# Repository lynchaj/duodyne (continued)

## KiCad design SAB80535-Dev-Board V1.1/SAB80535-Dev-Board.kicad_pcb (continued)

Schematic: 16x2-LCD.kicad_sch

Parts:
C13: 0.1uF; C_Disc_D5.0mm_W2.5mm_P5.00mm
J9: LCD PWR; PinHeader_2x03_P2.54mm_Vertical
J10: LCD PORT; PinHeader_2x08_P2.54mm_Vertical
RV2: 10K; Potentiometer_Bourns_3386P_Vertical

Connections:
A0: J10.5; also elsewhere on the board
A1: J10.4; also elsewhere on the board
D0: J10.7; also elsewhere on the board
D1: J10.8; also elsewhere on the board
D2: J10.9; also elsewhere on the board
D3: J10.10; also elsewhere on the board
D4: J10.11; also elsewhere on the board
D5: J10.12; also elsewhere on the board
D6: J10.13; also elsewhere on the board
D7: J10.14; also elsewhere on the board
E: J10.6; also elsewhere on the board
GND: C13.2, J9.1, J9.2, J10.16, RV2.3; also elsewhere on the board
LCD-ADJ: C13.1, J10.3, RV2.2
LCD-PWR1: J9.4, J10.1
LCD-PWR2: J9.3, J10.2
VCC: J9.5, J9.6, J10.15, RV2.1; also elsewhere on the board

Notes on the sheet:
NOTE: LCD APPEARS AT ~{CS-LCD} FF08-FF0B
NOTE: HD44780 interface https://www.pololu.com/product/773 16x2 2-LINE LCD DISPLAY

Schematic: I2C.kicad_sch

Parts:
BT1: Battery; BatteryHolder_Keystone_103_1x20mm
Brd1: SSD1306; 128x64OLED
J22: EXT I2C; PinHeader_1x04_P2.54mm_Vertical
J23: I2C INT; PinHeader_1x03_P2.54mm_Vertical
R15: 4700; R_Axial_DIN0207_L6.3mm_D2.5mm_P7.62mm_Horizontal
R18, R19: 10K; R_Axial_DIN0207_L6.3mm_D2.5mm_P7.62mm_Horizontal
U19: PCF8584; DIP-20_W7.62mm_Socket
U24: DS1307+; DIP-8_W7.62mm_Socket
X1: 32.768 KHz; Crystal_AT310_D3.0mm_L10.0mm_Horizontal

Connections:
/I2C/VBAT: BT1.1 (+), U24.3 (VBAT)
A0: U19.6 (A0); also elsewhere on the board
CLK: U19.1 (CLK); also elsewhere on the board
D0: U19.7 (D0); also elsewhere on the board
D1: U19.8 (D1); also elsewhere on the board
D2: U19.9 (D2); also elsewhere on the board
D3: U19.11 (D3); also elsewhere on the board
D4: U19.12 (D4); also elsewhere on the board
D5: U19.13 (D5); also elsewhere on the board
D6: U19.14 (D6); also elsewhere on the board
D7: U19.15 (D7); also elsewhere on the board
GND: BT1.2 (-), Brd1.1 (GND), J22.1, U19.10 (VSS), U24.4 (GND); also elsewhere on the board
I2C-SCL: Brd1.3 (SCL), J22.3, R18.1, U19.3 (SCL), U24.6 (SCL); also elsewhere on the board
I2C-SDA: Brd1.4 (SDA), J22.4, R19.1, U19.2 (SDA), U24.5 (SDA); also elsewhere on the board
unnamed: J23.2, R15.1, U19.5 (~INT)
unnamed: U24.1 (X1), X1.2
unnamed: U24.2 (X2), X1.1
VCC: Brd1.2 (VCC), J22.2, R15.2, R18.2, R19.2, U19.20 (VDD), U24.8 (VCC); also elsewhere on the board
~CS-I2C-WR: U19.18 (~WR); also elsewhere on the board
~CS-I2C: U19.17 (~CS); also elsewhere on the board
~INT0: J23.1; also elsewhere on the board
~INT1: J23.3; also elsewhere on the board
~OE: U19.16 (~RD); also elsewhere on the board
~RES-OUT: U19.19 (~RST); also elsewhere on the board

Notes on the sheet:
SSD1306 OLED 128x64 DISPLAY

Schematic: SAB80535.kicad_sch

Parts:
C31: 10u; CP_Radial_D5.0mm_P2.50mm
C33: 0.1uF; C_Disc_D5.0mm_W2.5mm_P5.00mm
D34: 1N4148; D_DO-35_SOD27_P7.62mm_Horizontal
J13: ~{PE} ~{EA}; PinHeader_2x03_P2.54mm_Vertical
J14: CMOS; PinHeader_1x02_P2.54mm_Vertical
J15: P1; IDC-Header_2x05_P2.54mm_Horizontal
J16: FE SS; PinHeader_1x04_P2.54mm_Vertical
J18: SAB80535; IDC-Header_2x13_P2.54mm_Horizontal
J19: MAIN & AUX SERIAL; IDC-Header_2x06_P2.54mm_Horizontal
J20: EXP BUS; IDC-Header_2x25_P2.54mm_Horizontal
J21: NMOS; PinHeader_1x02_P2.54mm_Vertical
J24: EXT RES; PinHeader_1x02_P2.54mm_Vertical
JP3: SER PWR MAIN; PinHeader_1x02_P2.54mm_Vertical
JP4: SER PWR AUX; PinHeader_1x02_P2.54mm_Vertical
JP5: RES SEL; PinHeader_1x03_P2.54mm_Vertical
R16: 10; R_Axial_DIN0207_L6.3mm_D2.5mm_P7.62mm_Horizontal
R17: 10K; R_Axial_DIN0207_L6.3mm_D2.5mm_P7.62mm_Horizontal
RN10: 10K; R_Array_SIP9
SW2: RESET; SW_PUSH_6mm
U12: SAB80C535; PLCC-68_THT-Socket
U13: 74LS373; DIP-20_W7.62mm_Socket
U16: 74LS74; DIP-14_W7.62mm_Socket
U20: 11.0592 MHz; DIP-14_W7.62mm_Socket
U21: DS1233; TO-92L_HandSolder

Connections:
/SAB80535/VBB: C33.1, J14.2, U12.37 (VCC)
A0: J20.5, U13.2 (O0); also elsewhere on the board
A1: J20.4, U13.5 (O1); also elsewhere on the board
A2: J20.3, U13.6 (O2); also elsewhere on the board
A3: J20.6, U13.9 (O3); also elsewhere on the board
A4: J20.9, U13.12 (O4); also elsewhere on the board
A5: J20.2, U13.15 (O5); also elsewhere on the board
A6: J20.7, U13.16 (O6); also elsewhere on the board
A7: J20.8, U13.19 (O7); also elsewhere on the board
A8: J20.10, U12.41 (P2.0); also elsewhere on the board
A9: J20.14, U12.42 (P2.1); also elsewhere on the board
A10: J20.12, U12.43 (P2.2); also elsewhere on the board
A11: J20.23, U12.44 (P2.3); also elsewhere on the board
A12: U12.45 (P2.4); also elsewhere on the board
A13: U12.46 (P2.5); also elsewhere on the board
A14: U12.47 (P2.6); also elsewhere on the board
A15: U12.48 (P2.7); also elsewhere on the board
ALE: U12.50 (ALE), U13.11 (LE); also elsewhere on the board
CLK: J20.11, U12.39 (XTAL2), U16.9 (Q); also elsewhere on the board
D0: J20.48, RN10.2 (R1), U12.52 (P0.0), U13.3 (D0), U16.2 (D); also elsewhere on the board
D1: J20.46, RN10.3 (R2), U12.53 (P0.1), U13.4 (D1); also elsewhere on the board
D2: J20.47, RN10.4 (R3), U12.54 (P0.2), U13.7 (D2); also elsewhere on the board
D3: J20.45, RN10.5 (R4), U12.55 (P0.3), U13.8 (D3); also elsewhere on the board
D4: J20.42, RN10.6 (R5), U12.56 (P0.4), U13.13 (D4); also elsewhere on the board
D5: J20.43, RN10.7 (R6), U12.57 (P0.5), U13.14 (D5); also elsewhere on the board
D6: J20.41, RN10.8 (R7), U12.58 (P0.6), U13.17 (D6); also elsewhere on the board
D7: J20.44, RN10.9 (R8), U12.59 (P0.7), U13.18 (D7); also elsewhere on the board
GND: C31.2, C33.2, J13.1, J13.2, J15.10, J16.2, J16.3, J18.26, J19.1, J19.2, J20.49, J20.50, J21.1, J24.2, SW2.2, U12.12 (VAGND), U12.38 (GND), U13.1 (OE), U13.10 (GND), U16.11 (C), U16.12 (D), U16.13 (~R), U20.4, U20.7, U21.1; also elsewhere on the board
I2C-SCL: J20.37; also elsewhere on the board
I2C-SDA: J20.39; also elsewhere on the board
unnamed: J19.5, JP3.2 (B)
unnamed: J19.6, JP4.2 (B)
unnamed: J21.2, U12.40 (XTAL1)
unnamed: J24.1, JP5.3, R16.1, SW2.1
unnamed: U16.10 (~S), U20.8, U20.11
ONE: U16.4 (~S); also elsewhere on the board
P1.0: J15.2, U12.36 (P1.0/~INT3/CC0); also elsewhere on the board
P1.1: J15.4, U12.35 (P1.1/INT4/CC1); also elsewhere on the board
P1.2: J15.6, U12.34 (P1.2/INT5/CC2); also elsewhere on the board
P1.3: J15.8, U12.33 (P1.3/INT6/CC3); also elsewhere on the board
P1.4: J15.7, U12.32 (P1.4/~INT2); also elsewhere on the board
P1.5: J15.5, U12.31 (P1.5/T2EX); also elsewhere on the board
P1.6: J15.3, U12.30 (P1.6/CLKOUT); also elsewhere on the board
P1.7: J15.1, U12.29 (P1.7/T2); also elsewhere on the board
P4.0: J18.2, U12.1 (P4.0); also elsewhere on the board
P4.1: J18.4, U12.2 (P4.1); also elsewhere on the board
P4.2: J18.6, U12.3 (P4.2); also elsewhere on the board
P4.3: J18.8, U12.5 (P4.3); also elsewhere on the board
P4.4: J18.10, U12.6 (P4.4); also elsewhere on the board
P4.5: J18.12, U12.7 (P4.5); also elsewhere on the board
P4.6: J18.14, U12.8 (P4.6); also elsewhere on the board
P4.7: J18.16, U12.9 (P4.7); also elsewhere on the board
P5.0: J18.18, U12.67 (P5.0); also elsewhere on the board
P5.1: J18.20, U12.66 (P5.1); also elsewhere on the board
P5.2: J18.22, U12.65 (P5.2); also elsewhere on the board
P5.3: J18.24, U12.64 (P5.3); also elsewhere on the board
P5.4: J18.23, U12.63 (P5.4); also elsewhere on the board
P5.5: J18.21, U12.62 (P5.5); also elsewhere on the board
P5.6: J18.19, U12.61 (P5.6); also elsewhere on the board
P5.7: J18.17, U12.60 (P5.7); also elsewhere on the board
P6.0: J18.1, U12.20 (P6.0)
P6.1: J18.3, U12.19 (P6.1)
P6.2: J18.5, U12.18 (P6.2)
P6.3: J18.7, U12.17 (P6.3)
P6.4: J18.9, U12.16 (P6.4)
P6.5: J18.11, U12.15 (P6.5)
P6.6: J18.13, U12.14 (P6.6)
P6.7: J18.15, U12.13 (P6.7)
RxD: U12.21 (P3.0/RxD); also elsewhere on the board
RxD-0: J19.7; also elsewhere on the board
RxD-1: J19.8; also elsewhere on the board
T0: U12.25 (P3.4/T0); also elsewhere on the board
T1: J16.4, U12.26 (P3.5/T1); also elsewhere on the board
TxD: U12.22 (P3.1/TxD); also elsewhere on the board
TxD-0: J19.9; also elsewhere on the board
TxD-1: J19.10; also elsewhere on the board
VCC: D34.1 (K), J13.5, J13.6, J14.1, J15.9, J18.25, J20.1, J20.22, JP3.1 (A), JP4.1 (A), R17.2, RN10.1 (common), U12.11 (VAREF), U12.68 (VCC), U13.20 (VCC), U20.1, U20.14, U21.3; also elsewhere on the board
ZA14: J20.24; also elsewhere on the board
ZA15: J20.25; also elsewhere on the board
ZA16: J20.28; also elsewhere on the board
ZA17: J20.27; also elsewhere on the board
ZA18: J20.30; also elsewhere on the board
ZA19: J20.29; also elsewhere on the board
ZA20: J20.32; also elsewhere on the board
ZA21: J20.31; also elsewhere on the board
~CS-FF-WR: U16.3 (C); also elsewhere on the board
~EA: J13.4, U12.51 (~EA)
~INT0: J20.33, U12.23 (P3.2/~INT0); also elsewhere on the board
~INT1: J16.1, J20.35, U12.24 (P3.3/~INT1); also elsewhere on the board
~OE: J20.26; also elsewhere on the board
~PAGE-EN: U16.6 (~Q); also elsewhere on the board
~PE: J13.3, U12.4 (~PE)
~PSEN: U12.49 (~PSEN); also elsewhere on the board
~RD: U12.28 (P3.7/~RD); also elsewhere on the board
~RES-IN: J20.40, JP5.2
~RES-OUT: C31.1, D34.2 (A), J20.38, JP5.1, R16.2, R17.1, U12.10 (~RESET), U16.1 (~R), U21.2; also elsewhere on the board
~WR: J20.21, U12.27 (P3.6/~WR); also elsewhere on the board
~Y1: J20.19; also elsewhere on the board
~Y2: J20.18; also elsewhere on the board
~Y7: J20.13; also elsewhere on the board

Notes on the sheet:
NOTE: SAB80C535 RESET IS ACTIVE LOW
NOTE: EXTERNAL PERIPHERALS APPEAR AT MEMORY LOCATIONS Y1 0xFF20-0xFF3F Y2 0xFF40-0xFF5F Y3 0xFF60-0xFF7F Y4 0xFF80-0xFF9F Y5 0xFFA0-0xFFBF Y6 0xFFC0-0xFFDF Y7 0xFFE0-0xFFFF
D-FLIP FLOP AS AN INVERTING DRIVER
JP14 NOTE: RESET SELECT ALLOWS FOR RESET TO ORIGINATE: 1. ON PROCESSOR BOARD RESET BUTTON CIRCUIT ONLY (NONE) 2. FROM EXTERNAL BUS ~{RES-IN} (1-2 CLOSED) 3. TRANSMITTED TO EXTERNAL BUS (2-3 CLOSED)
SINGLE STEP
~{EA} MUST BE TIED TO GND FOR SAB80535 OR SAB80C535 ACCESS EXTERNAL MEMORY
FLASH ERASE
~{PE} MUST BE TIED TO GND FOR SAB80C535 POWER SAVING MODES
P0.0-P0.7 MUST HAVE EXTERNAL PULL UP RESISTORS DURING PROGRAM VERIFICATION (SAB80C515 ONLY)

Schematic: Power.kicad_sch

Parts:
C14, C15, C16, C17, C18, C19, C20, C22, C23, C25, C27, C28, C32, C34, C36, C37, C38, C41, C42, C43: 0.1uF; C_Disc_D5.0mm_W2.5mm_P5.00mm
C21, C24, C26: 10uF; CP_Radial_D5.0mm_P2.50mm
C29, C30: 10u; CP_Radial_D5.0mm_P2.50mm
D10: 1N5819; D_DO-41_SOD81_P10.16mm_Horizontal
D11: VDD; LED_D3.0mm
D40: 9VDC; LED_D3.0mm
H1, H2, H3, H4: MountingHole; MountingHole_3.2mm_M3_Pad
J11: Barrel_Jack_MountingPin; BarrelJack_Horizontal
J12: 9VDC; TerminalBlock_Phoenix_MKDS-1,5-2-5.08_1x02_P5.08mm_Horizont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
NT1, NT3: NetTie_2; NetTie-2_THT_Pad0.3mm
R8: 470; R_Axial_DIN0207_L6.3mm_D2.5mm_P7.62mm_Horizontal
R12: 10K; R_Axial_DIN0207_L6.3mm_D2.5mm_P7.62mm_Horizontal
TP1: VCC; PinHeader_1x01_P2.54mm_Vertical
TP2: GND; PinHeader_1x01_P2.54mm_Vertical
U5: LM7805_TO220; TO-220-3_Horizontal_TabDown
U6: LP2950-3.3_TO92; TO-92_HandSolder

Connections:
/Power/9VDC: C18.1, D10.2 (A), J11.1, J12.1, R12.2
/Power/VI: C21.1, D10.1 (K), U5.1 (VI)
GND: C14.2, C15.2, C16.2, C17.2, C18.2, C19.2, C20.2, C21.2, C22.2, C23.2, C24.2, C25.2, C26.2, C27.2, C28.2, C29.2, C30.2, C32.2, C34.2, C36.2, C37.2, C38.2, C41.2, C42.2, C43.2, D11.1 (K), D40.1 (K), H1.1, H2.1, H3.1, H4.1, J11.2, J11.MP (MountPin), J12.2, NT1.1, TP2.1, U5.2 (GND), U6.2 (GND); also elsewhere on the board
unnamed: D11.2 (A), R8.1
unnamed: D40.2 (A), R12.1
ONE: NT3.2; also elsewhere on the board
VCC: C14.1, C15.1, C16.1, C17.1, C19.1, C20.1, C22.1, C23.1, C24.1, C25.1, C26.1, C27.1, C28.1, C29.1, C32.1, C34.1, C36.1, C37.1, C38.1, C41.1, C42.1, C43.1, NT3.1, TP1.1, U5.3 (VO), U6.3 (VI); also elsewhere on the board
VDD1: C30.1, R8.2, U6.1 (VO); also elsewhere on the board
ZERO: NT1.2; also elsewhere on the board

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
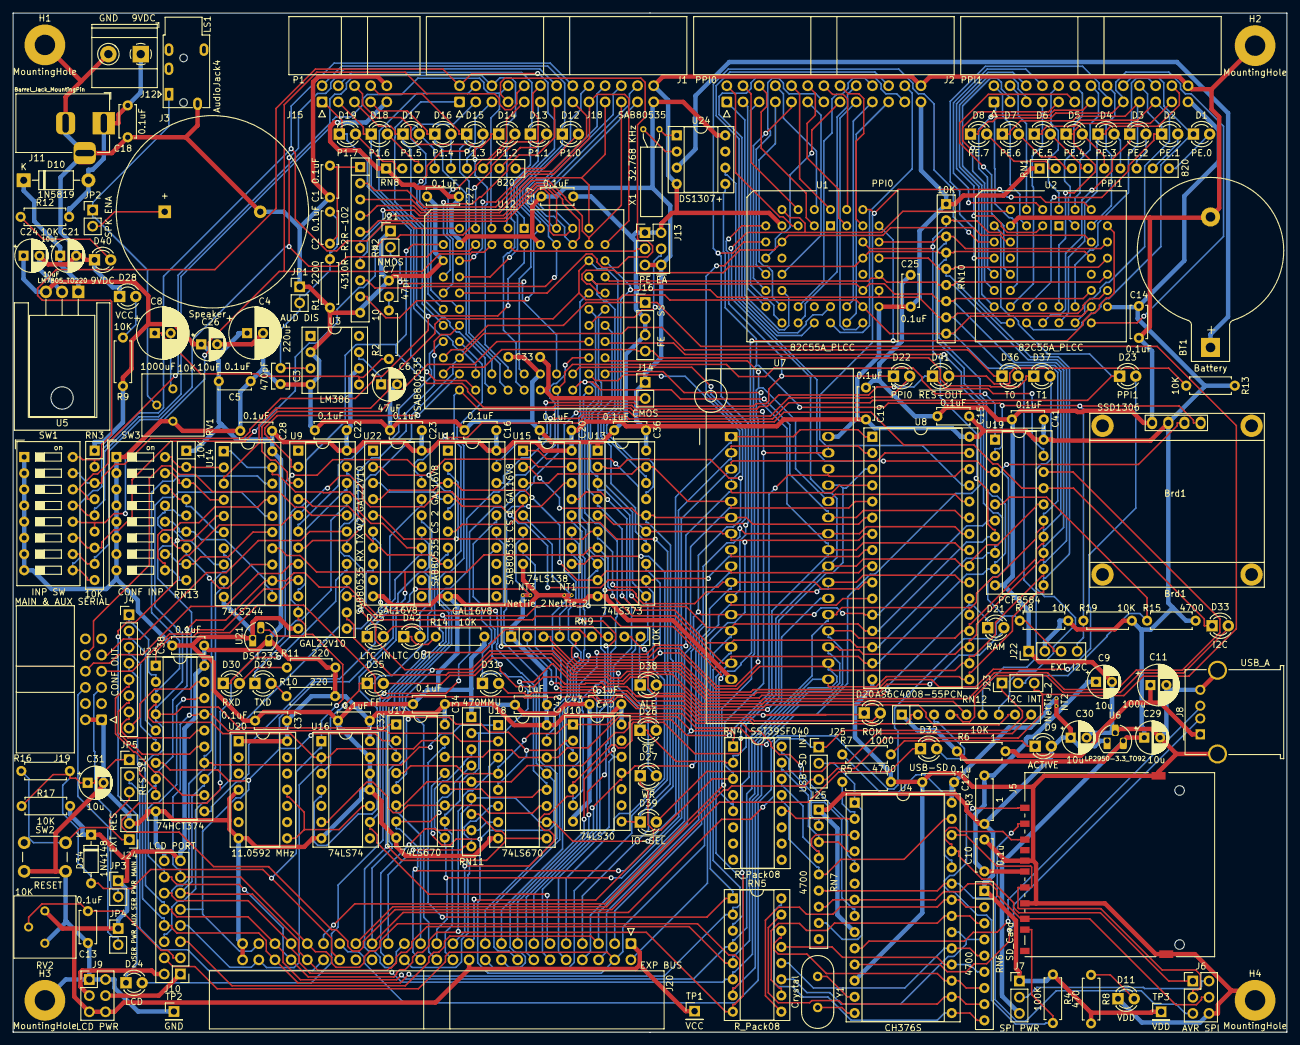
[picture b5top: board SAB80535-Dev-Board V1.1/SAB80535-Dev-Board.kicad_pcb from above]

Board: 2 copper layers, 200.0 x 160.0 mm, 187 parts (1 on the bottom side), 274 nets.

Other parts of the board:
RN11: 470; R_Array_SIP9
U17, U18: 74LS670; DIP-16_W7.62mm_Socket

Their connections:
A0: U17.14 (Wa), U18.14 (Wa); also elsewhere on the board
A1: U17.13 (Wb), U18.13 (Wb); also elsewhere on the board
A14: U17.5 (Ra), U18.5 (Ra); also elsewhere on the board
A15: U17.4 (Rb), U18.4 (Rb); also elsewhere on the board
D0: U17.15 (D1); also elsewhere on the board
D1: U17.1 (D2); also elsewhere on the board
D2: U17.2 (D3); also elsewhere on the board
D3: U17.3 (D4); also elsewhere on the board
D4: U18.15 (D1); also elsewhere on the board
D5: U18.1 (D2); also elsewhere on the board
D6: U18.2 (D3); also elsewhere on the board
D7: U18.3 (D4); also elsewhere on the board
GND: RN11.1 (common), U17.8 (GND), U18.8 (GND); also elsewhere on the board
VCC: U17.16 (VCC), U18.16 (VCC); also elsewhere on the board
ZA14: RN11.2 (R1), U17.10 (Q1); also elsewhere on the board
ZA15: RN11.3 (R2), U17.9 (Q2); also elsewhere on the board
ZA16: RN11.4 (R3), U17.7 (Q3); also elsewhere on the board
ZA17: RN11.5 (R4), U17.6 (Q4); also elsewhere on the board
ZA18: RN11.6 (R5), U18.10 (Q1); also elsewhere on the board
ZA19: RN11.7 (R6), U18.9 (Q2); also elsewhere on the board
ZA20: RN11.8 (R7), U18.7 (Q3); also elsewhere on the board
ZA21: RN11.9 (R8), U18.6 (Q4); also elsewhere on the board
~CS-MMU-WR: U17.12 (~Ew), U18.12 (~Ew); also elsewhere on the board
~PAGE-EN: U17.11 (~Er), U18.11 (~Er); also elsewhere on the board

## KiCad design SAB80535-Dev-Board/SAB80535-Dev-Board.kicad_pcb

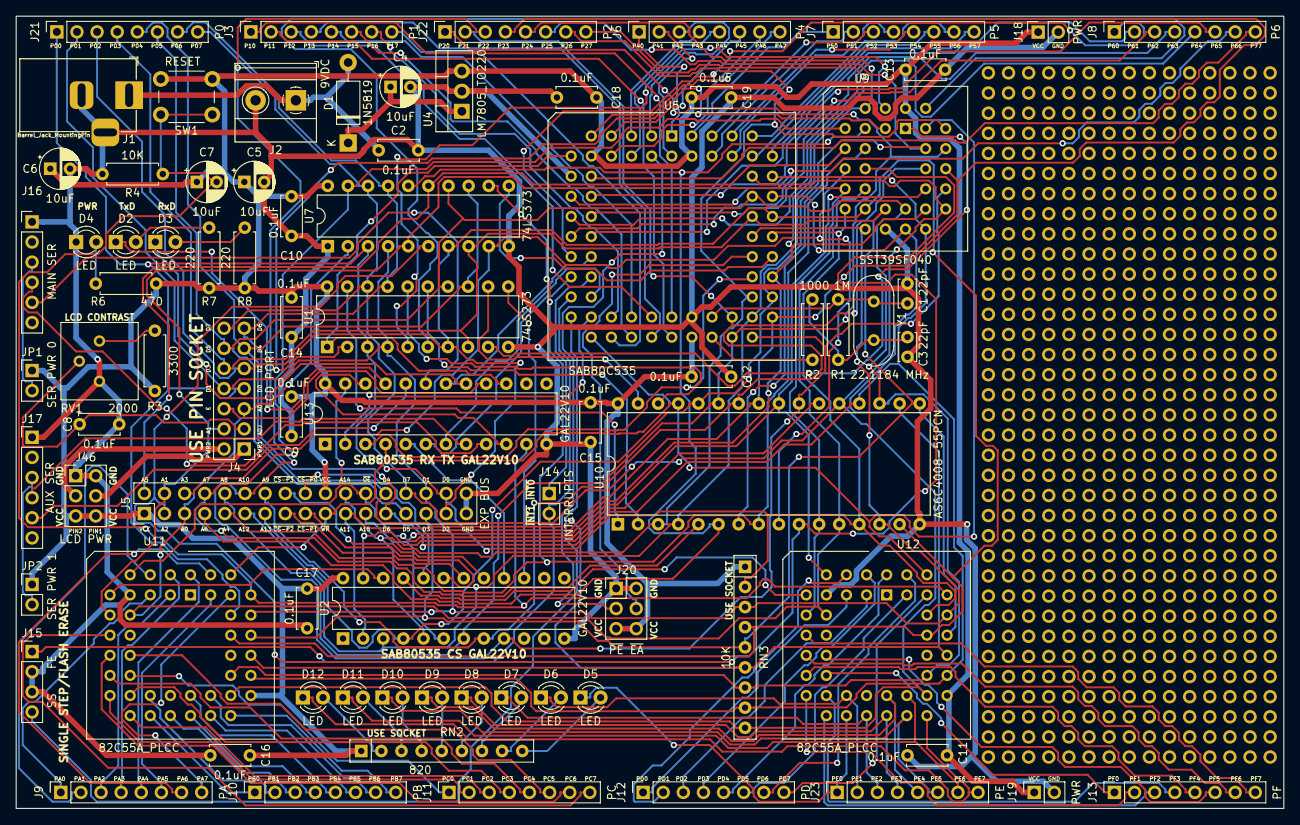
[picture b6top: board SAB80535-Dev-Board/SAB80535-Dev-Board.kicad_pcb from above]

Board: 2 copper layers, 160.0 x 100.0 mm, 100 parts (0 on the bottom side), 168 nets.

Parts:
C1, C3: 22pF; C_Disc_D3.4mm_W2.1mm_P2.50mm
C2, C8, C9, C10, C11, C12, C13, C14, C15, C16, C17, C18, C19: 0.1uF; C_Disc_D5.0mm_W2.5mm_P5.00mm
C4, C5, C6, C7: 10uF; CP_Radial_D5.0mm_P2.50mm
D1: 1N5819; D_DO-41_SOD81_P10.16mm_Horizontal
D2, D3, D4, D5, D6, D7, D8, D9, D10, D11, D12: LED; LED_D3.0mm
J1: Barrel_Jack_MountingPin; BarrelJack_Horizontal
J2: 9VDC; TerminalBlock_Phoenix_MKDS-1,5-2-5.08_1x02_P5.08mm_Horizont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
J3: P1; PinSocket_1x08_P2.54mm_Vertical
J4: LCD PORT; PinHeader_2x07_P2.54mm_Vertical
J5: EXP BUS; PinHeader_2x17_P2.54mm_Vertical
J6: P4; PinSocket_1x08_P2.54mm_Vertical
J7: P5; PinSocket_1x08_P2.54mm_Vertical
J8: P6; PinSocket_1x08_P2.54mm_Vertical
J9: PA; PinSocket_1x08_P2.54mm_Vertical
J10: PB; PinSocket_1x08_P2.54mm_Vertical
J11: PC; PinSocket_1x08_P2.54mm_Vertical
J12: PD; PinSocket_1x08_P2.54mm_Vertical
J13: PF; PinSocket_1x08_P2.54mm_Vertical
J14: INTERRUPTS; PinSocket_1x02_P2.54mm_Vertical
J15: SS FE; PinHeader_1x04_P2.54mm_Vertical
J16: MAIN SER; PinHeader_1x06_P2.54mm_Vertical
J17: AUX SER; PinHeader_1x06_P2.54mm_Vertical
J18, J19: PWR; PinSocket_1x02_P2.54mm_Vertical
J20: ~{PE} ~{EA}; PinHeader_2x03_P2.54mm_Vertical
J21: P0; PinSocket_1x08_P2.54mm_Vertical
J22: P2; PinSocket_1x08_P2.54mm_Vertical
J23: PE; PinSocket_1x08_P2.54mm_Vertical
J24, J25, J26, J27, J28, J29, J30, J31, J32, J33, J34, J35, J36, J37, J38, J39, J40, J41, J42, J43, J44: PTH; PTHelement
J46: LCD PWR; PinHeader_2x03_P2.54mm_Vertical
JP1: SER PWR 0; PinHeader_1x02_P2.54mm_Vertical
JP2: SER PWR 1; PinHeader_1x02_P2.54mm_Vertical
R1: 1M; R_Axial_DIN0207_L6.3mm_D2.5mm_P7.62mm_Horizontal
R2: 1000; R_Axial_DIN0207_L6.3mm_D2.5mm_P7.62mm_Horizontal
R3: 3300; R_Axial_DIN0207_L6.3mm_D2.5mm_P7.62mm_Horizontal
R4: 10K; R_Axial_DIN0207_L6.3mm_D2.5mm_P7.62mm_Horizontal
R6: 470; R_Axial_DIN0207_L6.3mm_D2.5mm_P7.62mm_Horizontal
R7, R8: 220; R_Axial_DIN0207_L6.3mm_D2.5mm_P7.62mm_Horizontal
RN2: 820; R_Array_SIP9
RN3: 10K; R_Array_SIP9
RV1: 2000; Potentiometer_Bourns_3386P_Vertical
SW1: RESET; SW_PUSH_6mm
U1: 74LS273; DIP-20_W7.62mm
U2, U13: GAL22V10; DIP-24_W7.62mm
U4: LM7805_TO220; TO-220-3_Vertical
U5: SAB80C535; PLCC-68_THT-Socket
U7: 74LS373; DIP-20_W7.62mm
U9: SST39SF040; PLCC-32_THT-Socket
U10: AS6C4008-55PCN; DIP-32_W15.24mm
U11, U12: 82C55A_PLCC; PLCC-44_THT-Socket
Y1: 22.1184 MHz; Crystal_HC49-4H_Vertical

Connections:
/9VDC: C2.1, D1.2 (A), J1.1, J2.1
/CS-LCD-WR: U13.10 (I9), U13.22 (O1)
/VI: C4.1, D1.1 (K), U4.1 (VI)
/XTAL1: C1.1, R1.1, U5.40 (XTAL1), Y1.1
/XTAL2: R2.2, U5.39 (XTAL2)
A0: J4.5, J5.5, U7.2 (O0), U9.12 (A0), U10.12 (A0), U11.10 (A0), U12.10 (A0)
A1: J4.4, J5.4, U7.5 (O1), U9.11 (A1), U10.11 (A1), U11.9 (A1), U12.9 (A1)
A2: J5.3, U7.6 (O2), U9.10 (A2), U10.10 (A2)
A3: J5.6, U7.9 (O3), U9.9 (A3), U10.9 (A3)
A4: J5.9, U7.12 (O4), U9.8 (A4), U10.8 (A4)
A5: J5.2, U7.15 (O5), U9.7 (A5), U10.7 (A5)
A6: J5.7, U7.16 (O6), U9.6 (A6), U10.6 (A6)
A7: J5.8, U7.19 (O7), U9.5 (A7), U10.5 (A7)
A8: J5.10, J22.1, U2.7 (I6), U5.41 (P2.0), U9.27 (A8), U10.27 (A8)
A9: J5.14, J22.2, U2.8 (I7), U5.42 (P2.1), U9.26 (A9), U10.26 (A9)
A10: J5.12, J22.3, U2.9 (I8), U5.43 (P2.2), U9.23 (A10), U10.23 (A10)
A11: J5.21, J22.4, U2.2 (I1), U5.44 (P2.3), U9.25 (A11), U10.25 (A11)
A12: J5.11, J22.5, U2.3 (I2), U5.45 (P2.4), U9.4 (A12), U10.4 (A12)
A13: J5.13, J22.6, U2.4 (I3), U5.46 (P2.5), U9.28 (A13), U10.28 (A13)
A14: J5.22, J22.7, U2.5 (I4), U5.47 (P2.6), U9.29 (A14), U10.3 (A14)
A15: J5.23, J22.8, U2.6 (I5), U5.48 (P2.7), U9.22 (CE)
ALE: U5.50 (ALE), U7.11 (LE)
B15: U1.2 (Q0), U9.3 (A15)
B16: U1.5 (Q1), U9.2 (A16)
B17: U1.6 (Q2), U9.30 (A17)
B18: U1.9 (Q3), U9.1 (A18)
C15: U1.12 (Q4), U10.31 (A15)
C16: U1.15 (Q5), U10.2 (A16)
C17: U1.16 (Q6), U10.30 (A17)
C18: U1.19 (Q7), U10.1 (A18)
D0: J4.7, J5.32, J21.1, RN3.2 (R1), U1.3 (D0), U5.52 (P0.0), U7.3 (D0), U9.13 (D0), U10.13 (DQ0), U11.38 (D0), U12.38 (D0)
D1: J4.8, J5.30, J21.2, RN3.3 (R2), U1.4 (D1), U5.53 (P0.1), U7.4 (D1), U9.14 (D1), U10.14 (DQ1), U11.37 (D1), U12.37 (D1)
D2: J4.9, J5.31, J21.3, RN3.4 (R3), U1.7 (D2), U5.54 (P0.2), U7.7 (D2), U9.15 (D2), U10.15 (DQ2), U11.36 (D2), U12.36 (D2)
D3: J4.10, J5.29, J21.4, RN3.5 (R4), U1.8 (D3), U5.55 (P0.3), U7.8 (D3), U9.17 (D3), U10.17 (DQ3), U11.35 (D3), U12.35 (D3)
D4: J4.11, J5.26, J21.5, RN3.6 (R5), U1.13 (D4), U5.56 (P0.4), U7.13 (D4), U9.18 (D4), U10.18 (DQ4), U11.33 (D4), U12.33 (D4)
D5: J4.12, J5.27, J21.6, RN3.7 (R6), U1.14 (D5), U5.57 (P0.5), U7.14 (D5), U9.19 (D5), U10.19 (DQ5), U11.32 (D5), U12.32 (D5)
D6: J4.13, J5.25, J21.7, RN3.8 (R7), U1.17 (D6), U5.58 (P0.6), U7.17 (D6), U9.20 (D6), U10.20 (DQ6), U11.31 (D6), U12.31 (D6)
D7: J4.14, J5.28, J21.8, RN3.9 (R8), U1.18 (D7), U5.59 (P0.7), U7.18 (D7), U9.21 (D7), U10.21 (DQ7), U11.30 (D7), U12.30 (D7)
E: J4.6, U13.16 (O7)
GND: C1.2, C2.2, C3.2, C4.2, C5.2, C6.2, C8.2, C9.2, C10.2, C11.2, C12.2, C13.2, C14.2, C15.2, C16.2, C17.2, C18.2, C19.2, D4.1 (K), J1.2, J1.MP (MountPin), J2.2, J5.33, J5.34, J15.2, J15.3, J16.1, J17.1, J18.2, J19.2, J20.1, J20.2, J46.1, J46.2, R4.2, RV1.3, U1.10 (GND), U2.12 (GND), U4.2 (GND), U5.12 (VAGND), U5.38 (GND), U7.1 (OE), U7.10 (GND), U9.16 (GND), U10.16 (VSS), U11.8 (GND), U12.8 (GND), U13.12 (GND)
LCD-ADJ: C8.1, J4.3, RV1.2
LCD-PWR1: J4.1, J46.4
LCD-PWR2: J4.2, J46.3
unnamed: C3.1, R1.2, R2.1, Y1.2
unnamed: D2.2 (A), R7.1
unnamed: D3.2 (A), R8.1
unnamed: D4.2 (A), R6.1
unnamed: D5.2 (A), RN2.9 (R8)
unnamed: D6.2 (A), RN2.8 (R7)
unnamed: D7.2 (A), RN2.7 (R6)
unnamed: D8.2 (A), RN2.6 (R5)
unnamed: D9.2 (A), RN2.5 (R4)
unnamed: D10.2 (A), RN2.4 (R3)
unnamed: D11.2 (A), RN2.3 (R2)
unnamed: D12.2 (A), RN2.2 (R1)
unnamed: J16.3, JP1.2 (B)
unnamed: J17.3, JP2.2 (B)
unnamed: R3.2, RV1.1
P1.0: J3.1, U5.36 (P1.0/~INT3/CC0)
P1.1: J3.2, U5.35 (P1.1/INT4/CC1)
P1.2: J3.3, U5.34 (P1.2/INT5/CC2)
P1.3: J3.4, U5.33 (P1.3/INT6/CC3)
P1.4: J3.5, U5.32 (P1.4/~INT2)
P1.5: J3.6, U5.31 (P1.5/T2EX)
P1.6: J3.7, U5.30 (P1.6/CLKOUT)
P1.7: J3.8, U5.29 (P1.7/T2)
P4.0: J6.1, U5.1 (P4.0)
P4.1: J6.2, U5.2 (P4.1)
P4.2: J6.3, U5.3 (P4.2)
P4.3: J6.4, U5.5 (P4.3)
P4.4: J6.5, U5.6 (P4.4)
P4.5: J6.6, U5.7 (P4.5)
P4.6: J6.7, U5.8 (P4.6)
P4.7: J6.8, U5.9 (P4.7)
P5.0: J7.1, U5.67 (P5.0)
P5.1: J7.2, U5.66 (P5.1)
P5.2: J7.3, U5.65 (P5.2)
P5.3: J7.4, U5.64 (P5.3)
P5.4: J7.5, U5.63 (P5.4)
P5.5: J7.6, U5.62 (P5.5)
P5.6: J7.7, U5.61 (P5.6)
P5.7: J7.8, U5.60 (P5.7)
P6.0: J8.1, U5.20 (P6.0)
P6.1: J8.2, U5.19 (P6.1)
P6.2: J8.3, U5.18 (P6.2)
P6.3: J8.4, U5.17 (P6.3)
P6.4: J8.5, U5.16 (P6.4)
P6.5: J8.6, U5.15 (P6.5)
P6.6: J8.7, U5.14 (P6.6)
P6.7: J8.8, U5.13 (P6.7)
PA.0: J9.1, U11.5 (PA0)
PA.1: J9.2, U11.4 (PA1)
PA.2: J9.3, U11.3 (PA2)
PA.3: J9.4, U11.2 (PA3)
PA.4: J9.5, U11.44 (PA4)
PA.5: J9.6, U11.43 (PA5)
PA.6: J9.7, U11.42 (PA6)
PA.7: J9.8, U11.41 (PA7)
PB.0: J10.1, U11.20 (PB0)
PB.1: J10.2, U11.21 (PB1)
PB.2: J10.3, U11.22 (PB2)
PB.3: J10.4, U11.24 (PB3)
PB.4: J10.5, U11.25 (PB4)
PB.5: J10.6, U11.26 (PB5)
PB.6: J10.7, U11.27 (PB6)
PB.7: J10.8, U11.28 (PB7)
PC.0: J11.1, U11.16 (PC0)
PC.1: J11.2, U11.17 (PC1)
PC.2: J11.3, U11.18 (PC2)
PC.3: J11.4, U11.19 (PC3)
PC.4: J11.5, U11.15 (PC4)
PC.5: J11.6, U11.14 (PC5)
PC.6: J11.7, U11.13 (PC6)
PC.7: J11.8, U11.11 (PC7)
PD.0: J12.1, U12.5 (PA0)
PD.1: J12.2, U12.4 (PA1)
PD.2: J12.3, U12.3 (PA2)
PD.3: J12.4, U12.2 (PA3)
PD.4: J12.5, U12.44 (PA4)
PD.5: J12.6, U12.43 (PA5)
PD.6: J12.7, U12.42 (PA6)
PD.7: J12.8, U12.41 (PA7)
PE.0: D5.1 (K), J23.1, U12.20 (PB0)
PE.1: D6.1 (K), J23.2, U12.21 (PB1)
PE.2: D7.1 (K), J23.3, U12.22 (PB2)
PE.3: D8.1 (K), J23.4, U12.24 (PB3)
PE.4: D9.1 (K), J23.5, U12.25 (PB4)
PE.5: D10.1 (K), J23.6, U12.26 (PB5)
PE.6: D11.1 (K), J23.7, U12.27 (PB6)
PE.7: D12.1 (K), J23.8, U12.28 (PB7)
PF.0: J13.1, U12.16 (PC0)
PF.1: J13.2, U12.17 (PC1)
PF.2: J13.3, U12.18 (PC2)
PF.3: J13.4, U12.19 (PC3)
PF.4: J13.5, U12.15 (PC4)
PF.5: J13.6, U12.14 (PC5)
PF.6: J13.7, U12.13 (PC6)
PF.7: J13.8, U12.11 (PC7)
RESET: C7.2, R4.1, SW1.1, U11.39 (RESET), U12.39 (RESET), U13.11 (I10)
RX-LED: D3.1 (K), U13.17 (O6)
RxD: U5.21 (P3.0/RxD), U13.18 (O5)
RxD-0: J16.4, U13.9 (I8)
RxD-1: J17.4, U13.8 (I7)
T0: U5.25 (P3.4/T0), U13.7 (I6)
T1: J15.4, U5.26 (P3.5/T1)
TX-LED: D2.1 (K), U13.21 (O2)
TxD: U5.22 (P3.1/TxD), U13.6 (I5)
TxD-0: J16.5, U13.19 (O4)
TxD-1: J17.5, U13.20 (O3)
VCC: C5.1, C6.1, C7.1, C9.1, C10.1, C11.1, C12.1, C13.1, C14.1, C15.1, C16.1, C17.1, C18.1, C19.1, J5.1, J5.20, J18.1, J19.1, J20.5, J20.6, J46.5, J46.6, JP1.1 (A), JP2.1 (A), R3.1, R6.2, R7.2, R8.2, RN2.1 (common), RN3.1 (common), SW1.2, U1.20 (VCC), U2.24 (VCC), U4.3 (VO), U5.11 (VAREF), U5.37 (VCC), U5.68 (VCC), U7.20 (VCC), U9.32 (VCC), U10.32 (VCC), U11.29 (VCC), U12.29 (VCC), U13.24 (VCC)
~CS-LATCH: U1.11 (Cp), U2.15 (O8)
~CS-LCD: U2.16 (O7), U13.5 (I4)
~CS-P0: J5.18, U2.20 (O3)
~CS-P1: J5.17, U2.19 (O4)
~CS-P2: J5.15, U2.18 (O5)
~CS-P3: J5.16, U2.17 (O6)
~CS-PPI0: U2.22 (O1), U11.7 (~CS)
~CS-PPI1: U2.21 (O2), U12.7 (~CS)
~CS-RAM: U2.23 (O0), U10.22 (CE#)
~EA: J20.4, U5.51 (~EA)
~INT0: J14.1, U5.23 (P3.2/~INT0)
~INT1: J14.2, J15.1, U5.24 (P3.3/~INT1)
~OE: J5.24, U9.24 (OE), U10.24 (OE#), U11.6 (~RD), U12.6 (~RD), U13.23 (O0)
~PE: J20.3, U5.4 (~PE)
~PSEN: U5.49 (~PSEN), U13.3 (I2)
~RD: U5.28 (P3.7/~RD), U13.2 (I1)
~RESET: U1.1 (~Mr), U5.10 (~RESET), U13.15 (O8)
~WR: J5.19, U5.27 (P3.6/~WR), U9.31 (PGM), U10.29 (WE#), U11.40 (~WR), U12.40 (~WR), U13.4 (I3)
